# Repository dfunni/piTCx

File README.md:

# piTCx
piTCx is a Raspberry Pi based roaster control system using Artisan Roasterscope as front-end UI. A Raspberry Pi can interface with the piTCx Power HAT+ to record temperatures from up to four thermocouples as well as the temperature sensor (MCP9800) on the piTCx board. For roaster control, the Raspberry Pi can perform heater control using slow PWM (1 Hz) with the Artisan software providing PID control. Heater control requires a solid state relay connected to the OT1 jumper on the piTCx HAT+. The piTCx Power HAT+ can also power the host Raspberry Pi over GPIO through the 5V jumper connection.

# piRoast Power
The piRoast Power is a complementary board provides  5V power to supply the Raspberry Pi via the piTCx Power HAT+. Additionally, the board contains a solid state relay for heater control.

# Raspberry Pi Setup
Starting with a fresh install of the latest raspbian OS (tested with Bookworm):

1. configure the raspi with
```
sudo raspi-config
```    
In the "Advanced" menu, select expand filesystem.

In the "Interfaces" menu enable ssh, I2C, Serial Port, and Remote GPIO.

Reboot to finish the configuration.

2. Install required tools
```
sudo apt install socat
```
3. Ensure pigpiod is enabled and running
```
sudo systemctl enable pigpiod
sudo systemctl start pigpiod
```
4. Install Artisan
```
curl -L -O https://github.com/artisan-roaster-scope/artisan/releases/download/<vx.xx.x>/<artisan-linux-x.xx.x.deb>
sudo dpkg -i <artisan-linux-x.x.x.deb>
```
5. Download and setup the piTCx code
```
git clone https://github.com/dfunni/piTCx.git
cd piTCx
python -m venv env
source env/bin/activate
pip install -r requirements.txt
```
6. Create systemd service to run the piTCx command interface. First update tcxd.service line 10 to the correct login user (e.g. pi). Then:
```
sudo cp tcxd.service /etc/systemd/system/
sudo systemctl enable tcxd.service
```
From here everything is setup and ready. The next steps are to configure Artisan for communication with the TCx board.

## (Optional) Launch Artisan on boot
Copy `start_artisan.sh` to `/etc/profile.d/` with:
```
sudo cp $HOME/piTCx/start_artisan.sh /etc/profile.d/
```
# Artisan Setup
1. Go to Config > Device
    - at the top of the ET/BT tab check Control, Curves: BT, LCDs: ET and BT
    - select TC4 radio button, set ET and BT channels, set AT Channel to None, deselect PID Firmware
    - in the Extra Devices tab add the following:
        ArduinoTC4_56; Label 1: Heater; Label 2: Fan; Curve 1: enable; Curve 2: enable
        ArduinoTC4_78; Label 1: SV; Label 2: Ambient; LCD 2: enable; Curve 1: enable; Curve 2: enable

2. In Ports set Comm Port to /dev/ttyS91 with 115200-8-N-1 and change the serial Timeout to **0.4** seconds

3. Config > Sampling set to 1.0 seconds, accept the popup

4. Config > Curves select BT Projection and set to linear

5. Config > Events
     - set Event Types 2 to Heater and have that as the only event tyupe slected
     - set Default Buttons - DROP to Serial Command: OT1;0
     - under the Buttons Tab add the following
        Heater MAX; Type: Heater; Value: 100; Action: Serial Command; Documentation: OT1;{}
        Heater Off; Type: Heater; Value: 0; Action: Serial Command; Documentation: OT1;{}
        PID OFF; Type: Heater Value: 0; Action: Artisan Command; Documentation: PIDoff
    - Sliders - Event: Heater; Action: Serial Command; Command: OT1;{}

6. Config > Temperature > Celcius Mode

7. Roast > Background
    - show, BT selected
    - Load background .alog file

8. Control (Button)
    - kp: 1.30
    - ki: 0.06
    - kd: 4.50
    - Source: BT; Target - Positive: Heater; Set Value - Mode: Background; Set PID on CHARGE: enabled

# Testing piTCx on Raspberry Pi
1. Ensure Raspberry Pi setup is completed per instructions in Raspberry Pi Setup
  section. Ensure piTCx HAT+ is connected.

3. In the ~/piTCx directory run pytests with:
```
cd ~/piTCx
pytest --cov
```

3. Navigate to the ~/piTCx/tests/ directory and run:
```
cd tests/
./integration_test.sh
```
Monitor the output to ensure temperatures are read, no errors are produced.

4. Run the sample rate test to ensure 1.0 second sampling intervals are working:
```
./samprate_test.sh
```
Monitor the output to esure 10 reads are taken. Check the timestamps for 1 second accuracy. 

5. Additionally, a single Artisan command can be executed with:
```
./ArtisonCMD.sh <command> [<value>]
```
 using a command value pair from the following:
| command | value | notes |
| ------- | ----- | ----- |
| CHAN    | 1234  | Initializes the piTCx and sets order of ADC channels |
| READ    |       | No value for READ command |
| UNITS   | F/C   | Temperature units to be read |
| OT1     | 0-100 | Sets OT1 duty cycle |
| OT2     | 0-100 | Sets OT2 duty cycle |
| IO2     | 0-100 | Sets IO2 duty cycle |

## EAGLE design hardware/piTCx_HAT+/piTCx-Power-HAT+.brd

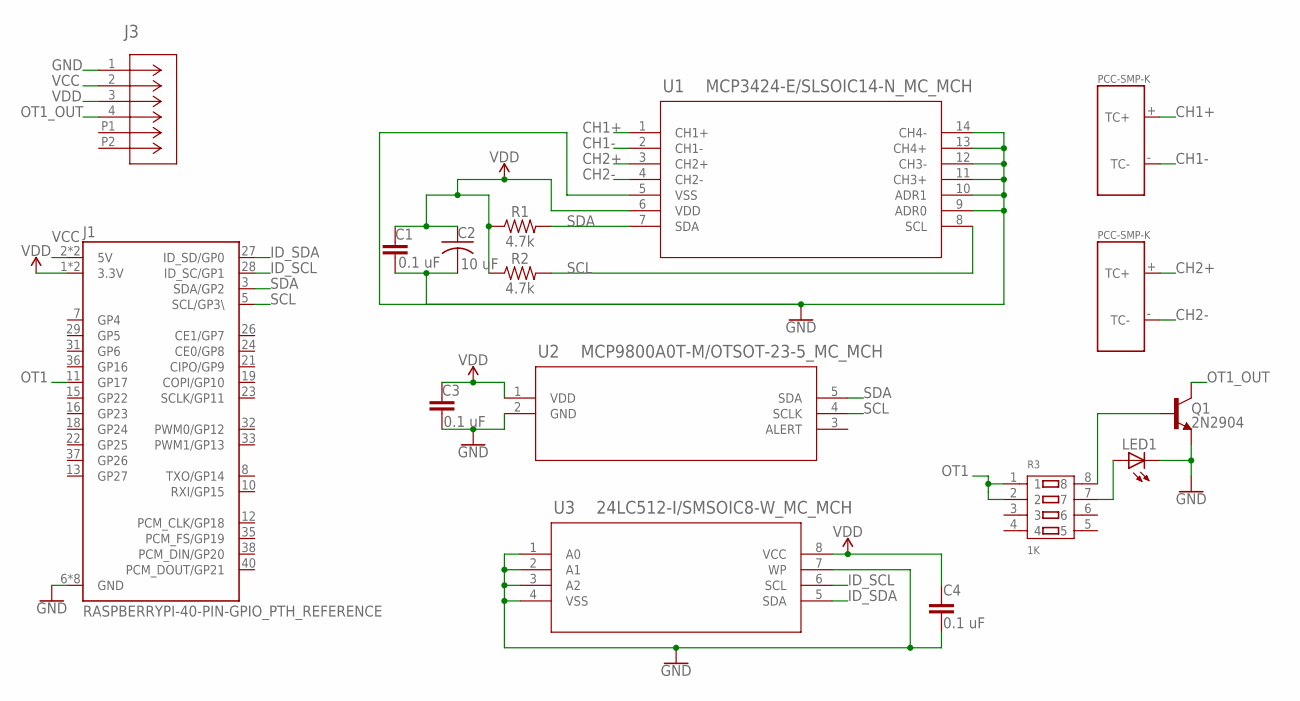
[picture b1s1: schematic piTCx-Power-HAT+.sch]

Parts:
C1, C3, C4: 0.1 uF; CAP_0805
C2: 10 uF; CAP_TANT_B; MPN T494A106M020AT
J1: RASPBERRYPI-40-PIN-GPIO_PTH_REFERENCE; RASPBERRY_PI_HAT_40_PIN_PTH_WITH_REFERNCE
J3: 436500414CON_436500414; CON_436500414
LED1: LEDCHIP-LED0805; CHIP-LED0805
Q1: 2N2904; SOT23-3
R1, R2: 4.7k; 0603
R3: 1K; RA1206-8
U1: MCP3424-E/SLSOIC14-N_MC_MCH; SOIC14-N_MC_MCH
U2: MCP9800A0T-M/OTSOT-23-5_MC_MCH; SOT-23-5_MC_MCH
U3: 24LC512-I/SMSOIC8-W_MC_MCH; SOIC8-W_MC_MCH
U$1, U$2: THERMOCOUPLECONN-PCC-SMP-K

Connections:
CH1+: U1.1 (CH1+), U$1.+ (TC+)
CH1-: U1.2 (CH1-), U$1.- (TC-)
CH2+: U1.3 (CH2+), U$2.+ (TC+)
CH2-: U1.4 (CH2-), U$2.- (TC-)
GND: C1.2, C2.2, C3.2, C4.2, J1.6 (GND), J1.9 (GND), J1.14 (GND), J1.20 (GND), J1.25 (GND), J1.30 (GND), J1.34 (GND), J1.39 (GND), J3.1, LED1.C, Q1.2 (E), U1.5 (VSS), U1.9 (ADR0), U1.10 (ADR1), U1.11 (CH3+), U1.12 (CH3-), U1.13 (CH4+), U1.14 (CH4-), U2.2 (GND), U3.1 (A0), U3.2 (A1), U3.3 (A2), U3.4 (VSS), U3.7 (WP)
ID_SCL: J1.28 (ID_SC/GP1), U3.6 (SCL)
ID_SDA: J1.27 (ID_SD/GP0), U3.5 (SDA)
unnamed: Q1.1 (B), R3.8
unnamed: LED1.A, R3.7
OT1: J1.11 (GP17), R3.1, R3.2
OT1_OUT: J3.4, Q1.3 (C)
SCL: J1.5 (SCL/GP3\), R2.2, U1.8 (SCL), U2.4 (SCLK)
SDA: J1.3 (SDA/GP2), R1.2, U1.7 (SDA), U2.5 (SDA)
VCC: J1.2 (5V), J1.4 (5V), J3.2
VDD: C1.1, C2.1, C3.1, C4.1, J1.1 (3.3V), J1.17 (3.3V), J3.3, R1.1, R2.1, U1.6 (VDD), U2.1 (VDD), U3.8 (VCC)

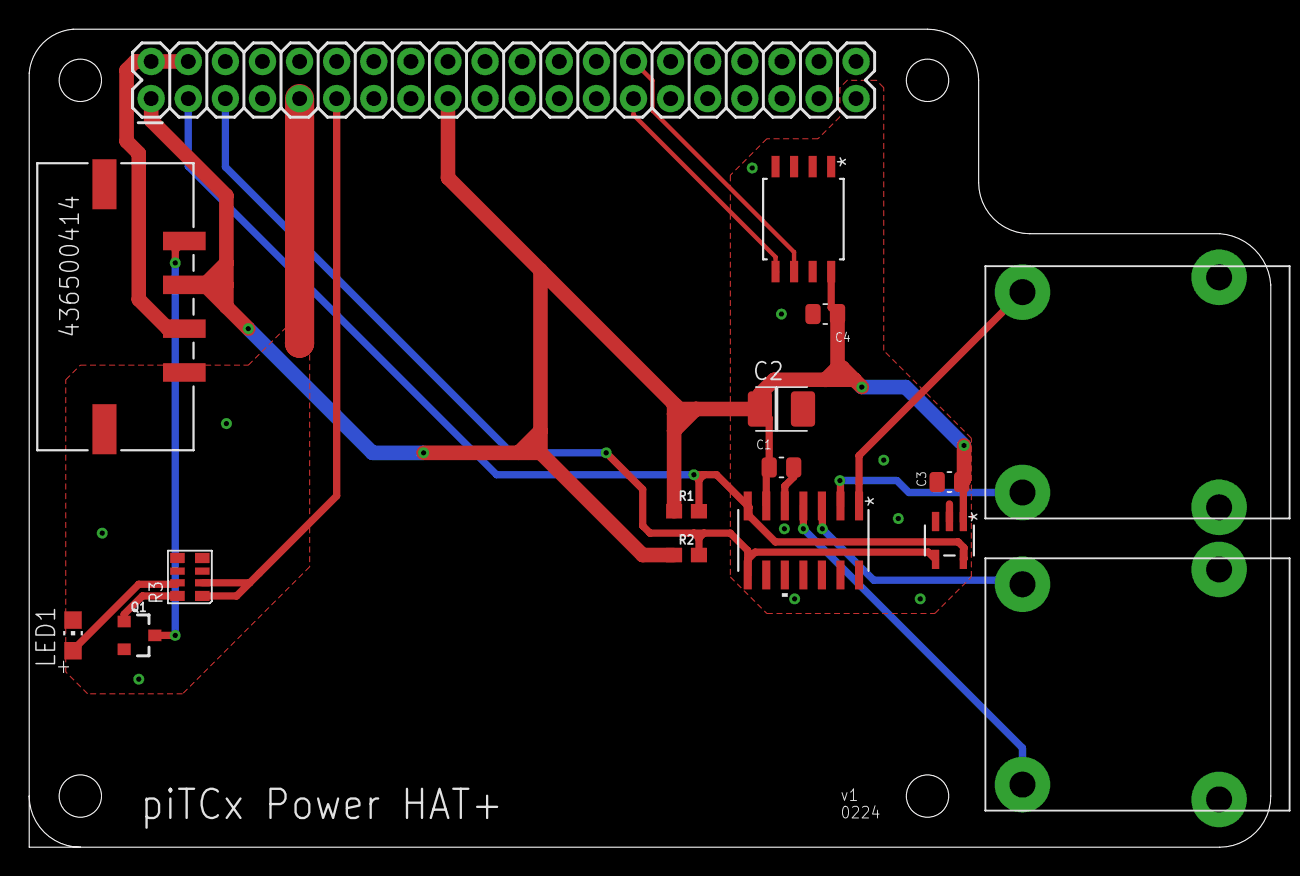
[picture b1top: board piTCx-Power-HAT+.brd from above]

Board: 2 copper layers, 85.0 x 56.0 mm, 16 parts (0 on the bottom side), 15 nets.

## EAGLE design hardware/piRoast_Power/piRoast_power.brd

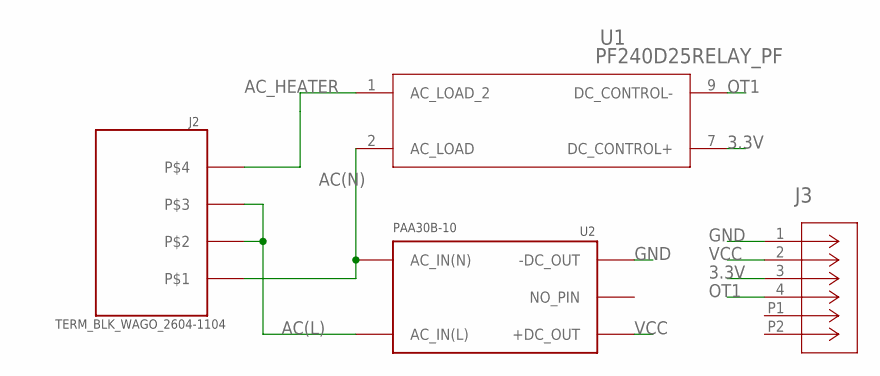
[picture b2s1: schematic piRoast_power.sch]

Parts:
J2: TERM_BLK_WAGO_2604-1104
J3: 436500414CON_436500414; CON_436500414
U1: PF240D25RELAY_PF; RELAY_PF
U2: PAA30B-10

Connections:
3.3V: J3.3, U1.7 (DC_CONTROL+)
AC(L): J2.P1, J2.P2, J2.P5, J2.P6, U2.AC_IN(L)
AC(N): J2.P3, J2.P4, U1.2 (AC_LOAD), U2.AC_IN(N)
AC_HEATER: J2.P0, J2.P7, U1.1 (AC_LOAD_2)
GND: J3.1, U2.-DC_OUT
OT1: J3.4, U1.9 (DC_CONTROL-)
VCC: J3.2, U2.+DC_OUT

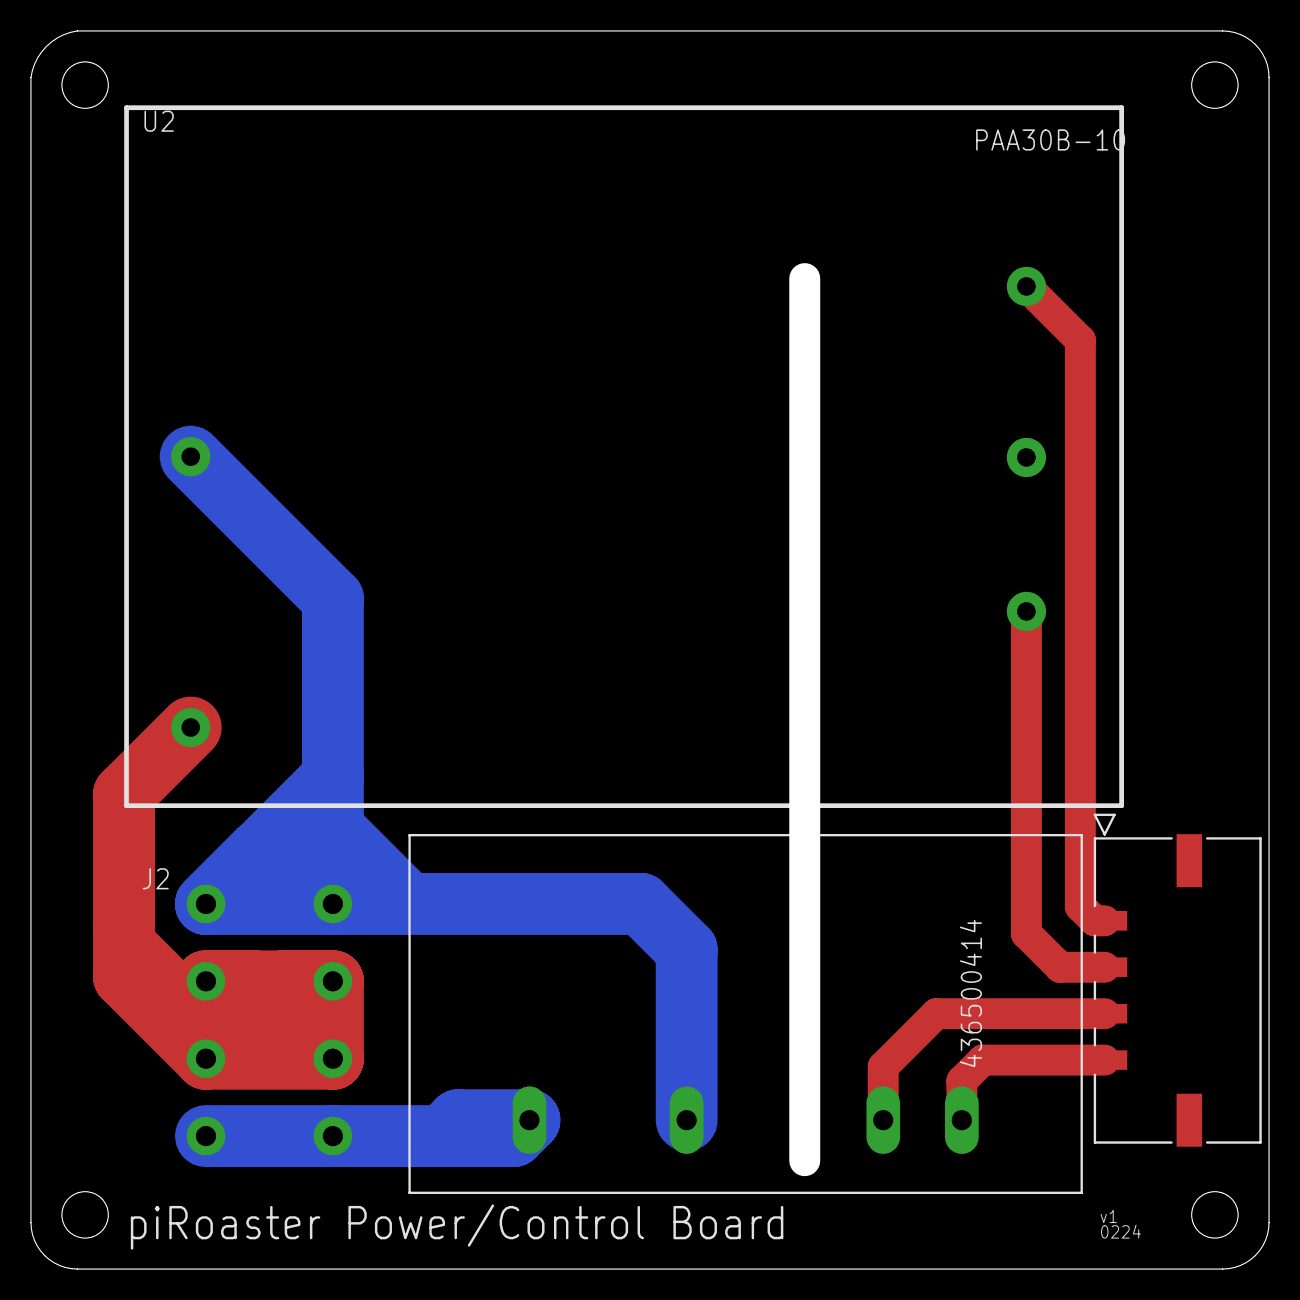
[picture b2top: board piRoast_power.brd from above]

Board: 2 copper layers, 80.0 x 80.0 mm, 4 parts (0 on the bottom side), 7 nets.

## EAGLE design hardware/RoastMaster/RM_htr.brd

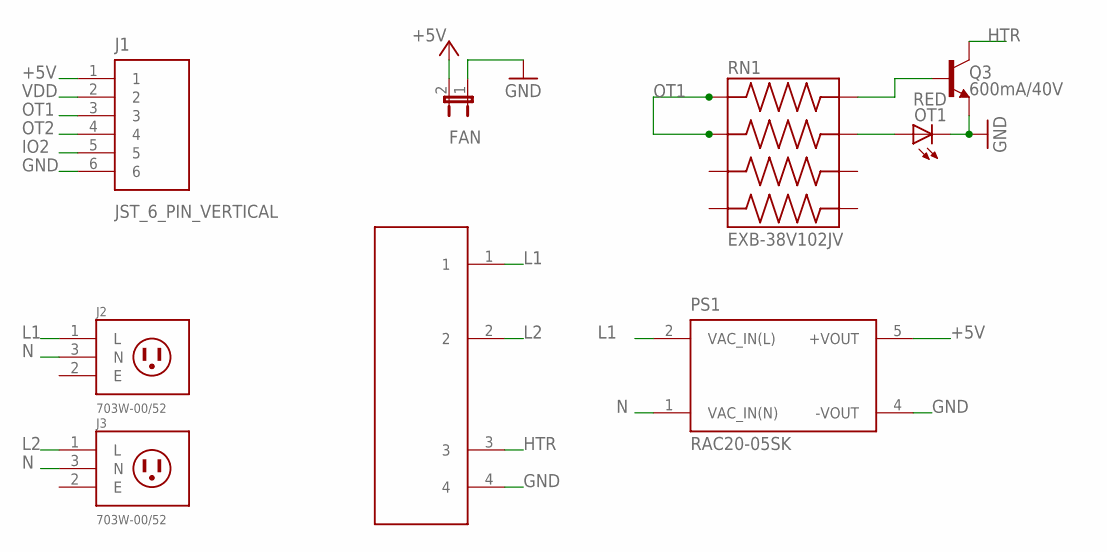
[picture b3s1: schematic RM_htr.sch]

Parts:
FAN: JP1E; JP1
J1: JST_6_PIN_VERTICAL; JST-6-SMD-VERT-1.0MM
J2, J3: 703W-00/52; QUALTEK_703W-00/52
OT1: RED; CHIPLED_0805
PS1: RAC20-05SK; CONV_RAC20-05SK
Q3: 600mA/40V; SOT23-3
RN1: EXB-38V102JV; RESCAXS80P320X160X60-8N
U$1: PF240D25X

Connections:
+5V: FAN.2, J1.1, PS1.5 (+VOUT)
E: J2.2 (E), J3.2 (E)
GND: FAN.1, J1.6, OT1.C, PS1.4 (-VOUT), Q3.2 (E), U$1.4
HTR: Q3.3 (C), U$1.3
IO2: J1.5
L1: J2.1 (L), PS1.2 (VAC_IN(L)), U$1.1
L2: J3.1 (L), U$1.2
N: J2.3 (N), J3.3 (N), PS1.1 (VAC_IN(N))
unnamed: Q3.1 (B), RN1.8
unnamed: OT1.A, RN1.7
OT1: J1.3, RN1.1, RN1.2
OT2: J1.4
VDD: J1.2

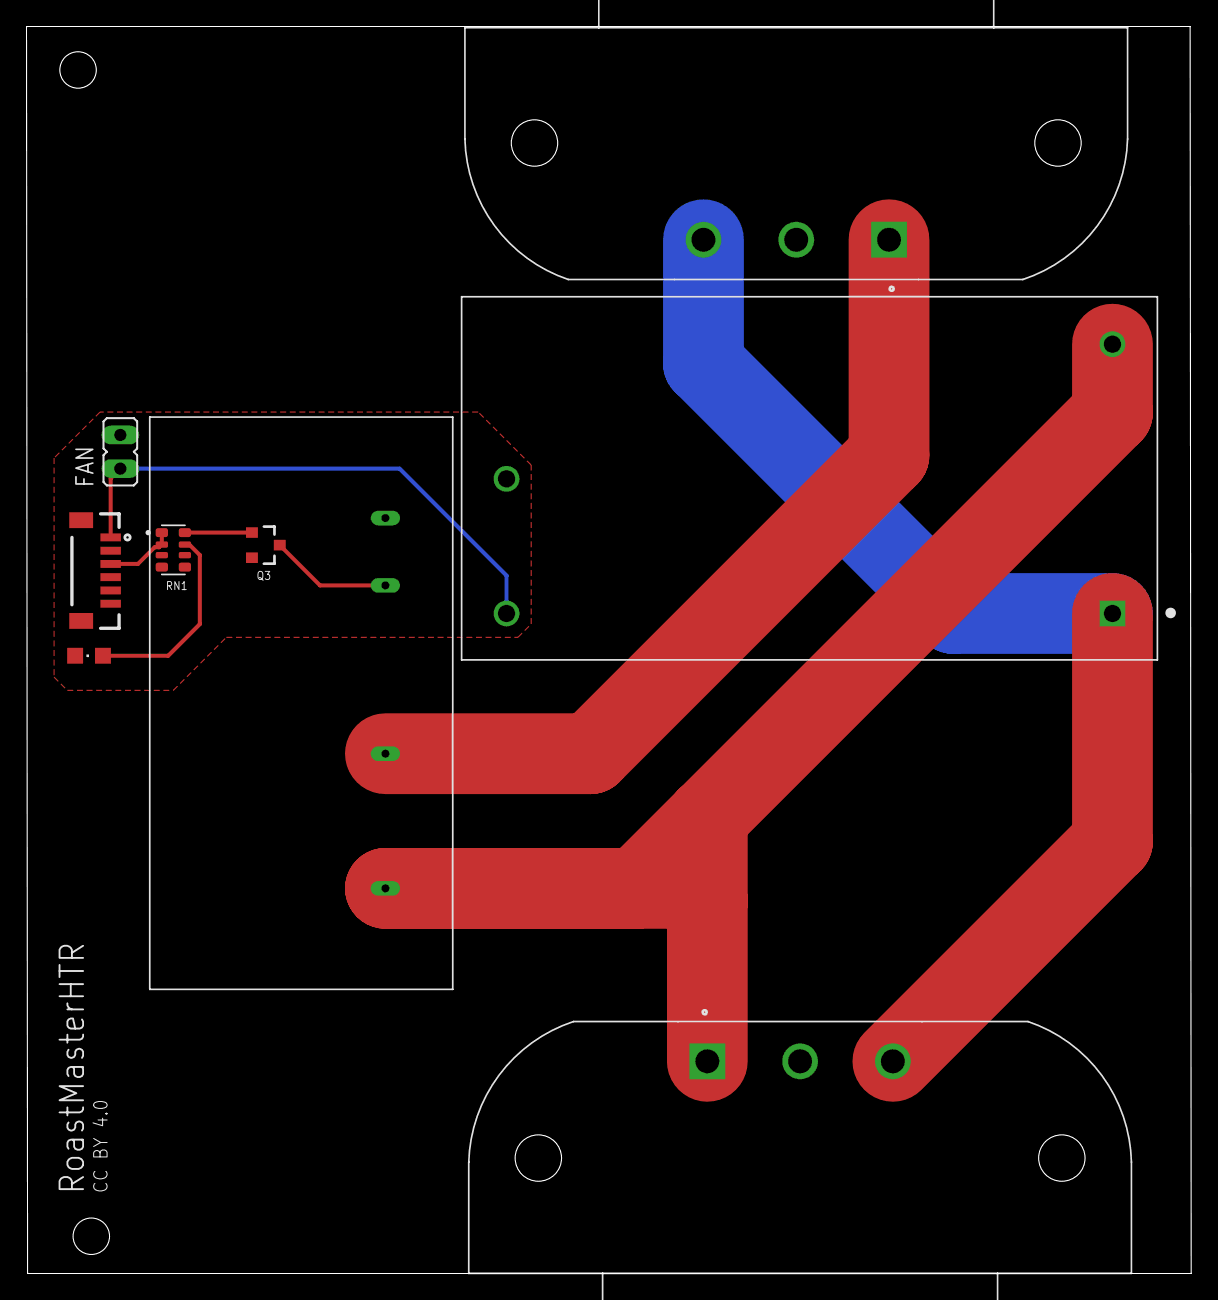
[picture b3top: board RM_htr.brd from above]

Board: 2 copper layers, 87.9 x 94.1 mm, 9 parts (0 on the bottom side), 10 nets.

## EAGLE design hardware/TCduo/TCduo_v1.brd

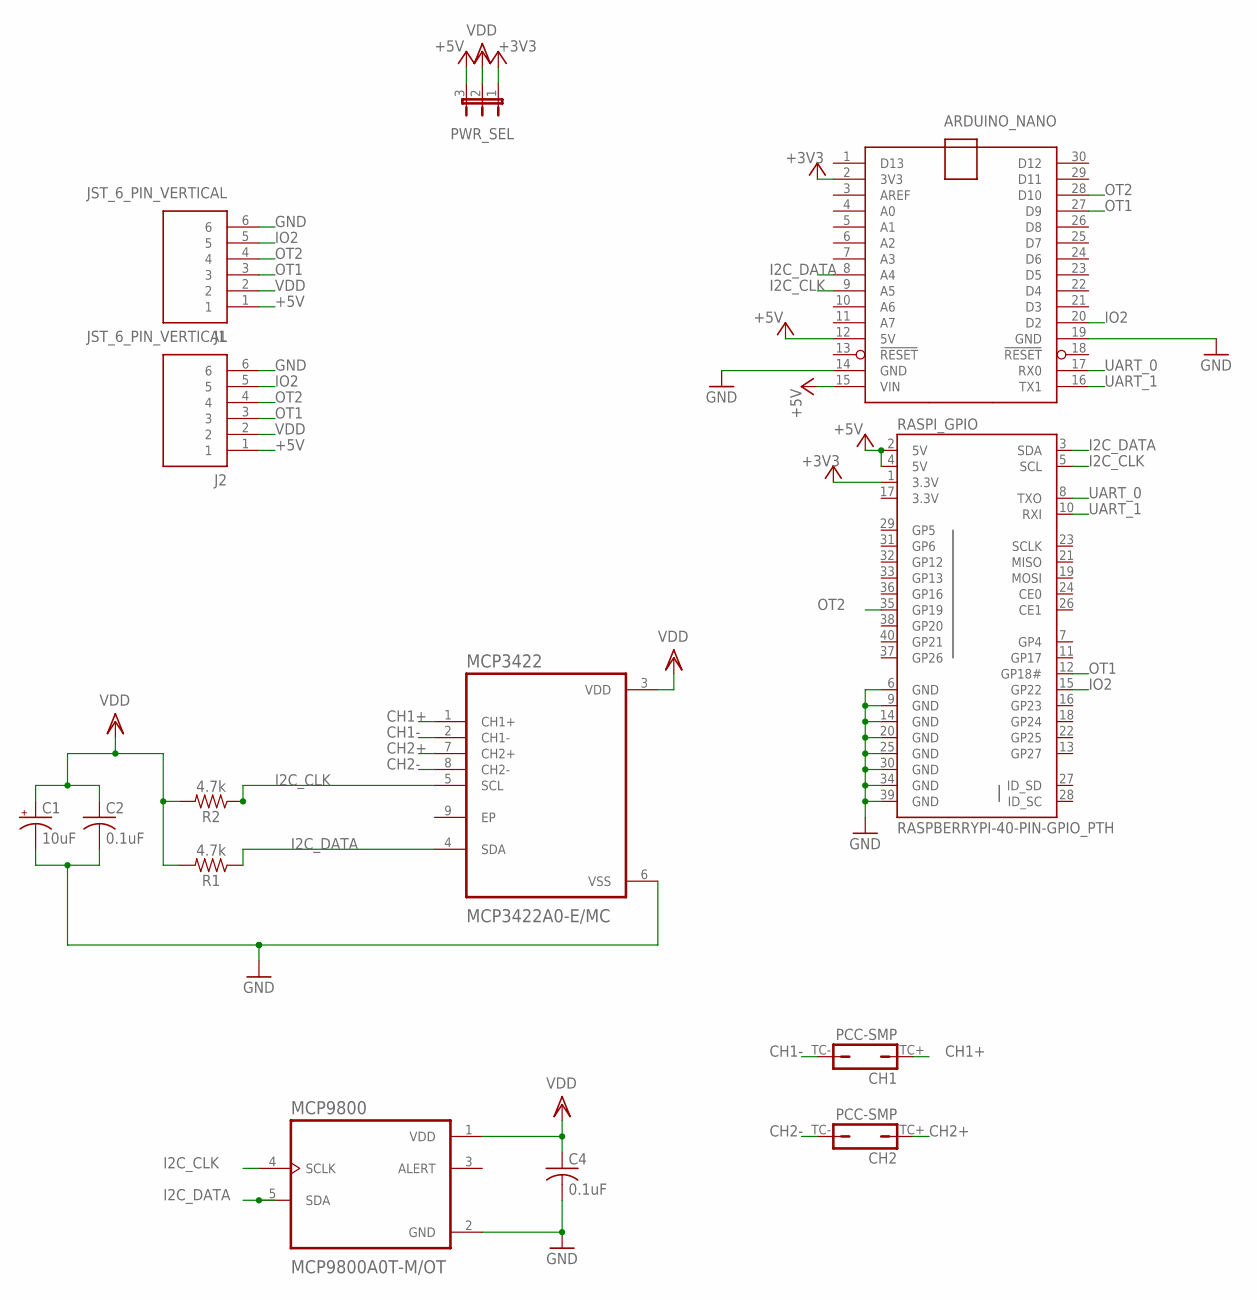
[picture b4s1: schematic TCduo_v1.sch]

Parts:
ARDUINO_NANO: ARDUINO_NANO
C1: 10uF; EIA3216
C2, C4: 0.1uF; C0805
CH1, CH2: PCC-SMP
J1, J2: JST_6_PIN_VERTICAL; JST-6-SMD-VERT-1.0MM
MCP3422: MCP3422A0-E/MC; SON50P200X300X100-9N
MCP9800: MCP9800A0T-M/OT; SOT95P270X145-5N
PWR_SEL: JP2E; JP2
R1, R2: 4.7k; 0603
RASPI_GPIO: RASPBERRYPI-40-PIN-GPIO_PTH; 2X20_SHROUDED

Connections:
3.3V: RASPI_GPIO.17 (3.3V)
+3V3: ARDUINO_NANO.2 (3V3), PWR_SEL.1, RASPI_GPIO.1 (3.3V)
+5V: ARDUINO_NANO.12 (5V), ARDUINO_NANO.15 (VIN), J1.1, J2.1, PWR_SEL.3, RASPI_GPIO.2 (5V), RASPI_GPIO.4 (5V)
CH1+: CH1.TC+ (1), MCP3422.1 (CH1+)
CH1-: CH1.TC- (2), MCP3422.2 (CH1-)
CH2+: CH2.TC+ (1), MCP3422.7 (CH2+)
CH2-: CH2.TC- (2), MCP3422.8 (CH2-)
GND: ARDUINO_NANO.14 (GND), ARDUINO_NANO.19 (GND), C1.-, C2.2, C4.2, J1.6, J2.6, MCP3422.6 (VSS), MCP9800.2 (GND), RASPI_GPIO.6 (GND), RASPI_GPIO.9 (GND), RASPI_GPIO.14 (GND), RASPI_GPIO.20 (GND), RASPI_GPIO.25 (GND), RASPI_GPIO.30 (GND), RASPI_GPIO.34 (GND), RASPI_GPIO.39 (GND)
I2C_CLK: ARDUINO_NANO.9 (A5), MCP3422.5 (SCL), MCP9800.4 (SCLK), R2.1, RASPI_GPIO.5 (SCL)
I2C_DATA: ARDUINO_NANO.8 (A4), MCP3422.4 (SDA), MCP9800.5 (SDA), R1.1, RASPI_GPIO.3 (SDA)
IO2: ARDUINO_NANO.20 (D2), J1.5, J2.5, RASPI_GPIO.15 (GP22)
OT1: ARDUINO_NANO.27 (D9), J1.3, J2.3, RASPI_GPIO.12 (GP18#)
OT2: ARDUINO_NANO.28 (D10), J1.4, J2.4, RASPI_GPIO.35 (GP19)
UART_0: ARDUINO_NANO.17 (RX0), RASPI_GPIO.8 (TXO)
UART_1: ARDUINO_NANO.16 (TX1), RASPI_GPIO.10 (RXI)
VDD: C1.+, C2.1, C4.1, J1.2, J2.2, MCP3422.3 (VDD), MCP9800.1 (VDD), PWR_SEL.2, R1.2, R2.2

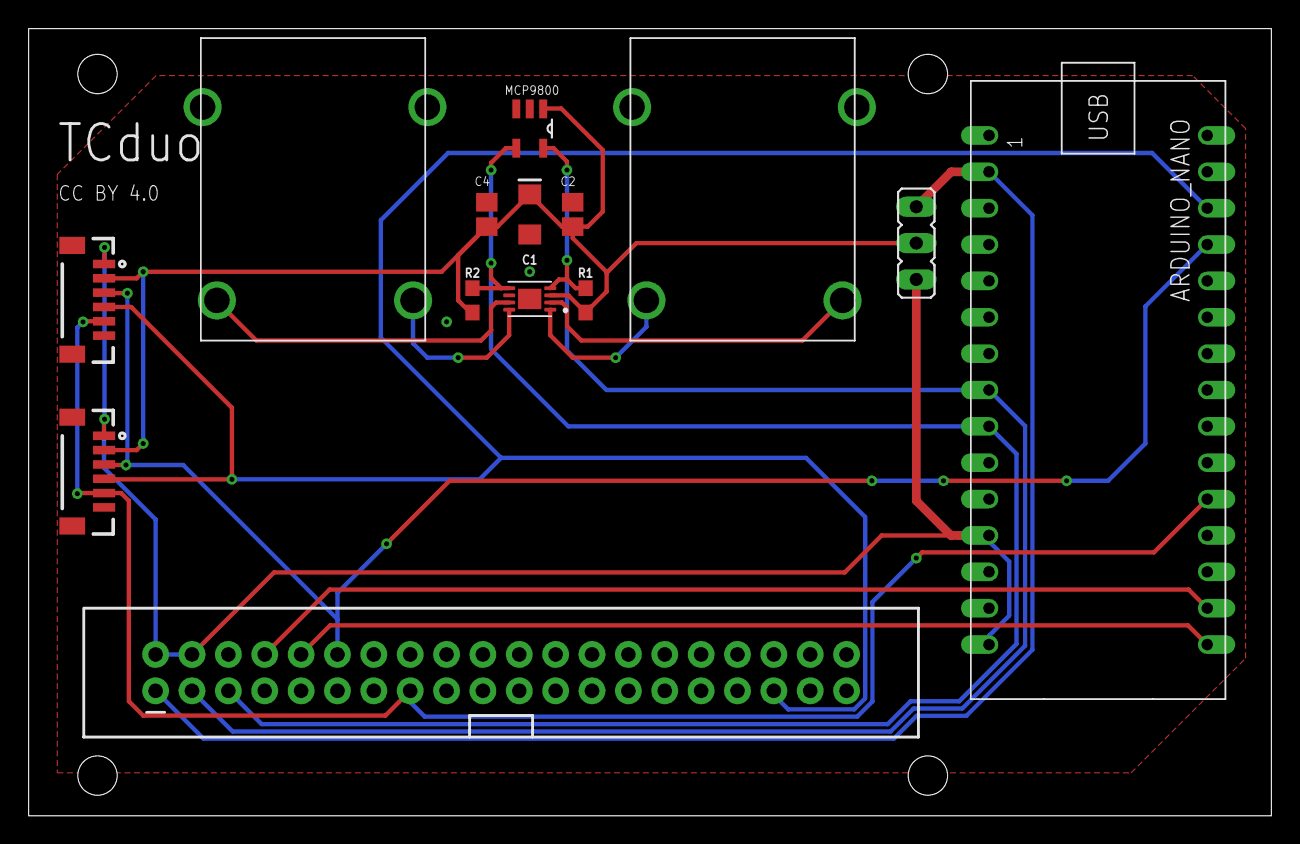
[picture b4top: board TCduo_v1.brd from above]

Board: 2 copper layers, 86.8 x 55.0 mm, 14 parts (0 on the bottom side), 15 nets.

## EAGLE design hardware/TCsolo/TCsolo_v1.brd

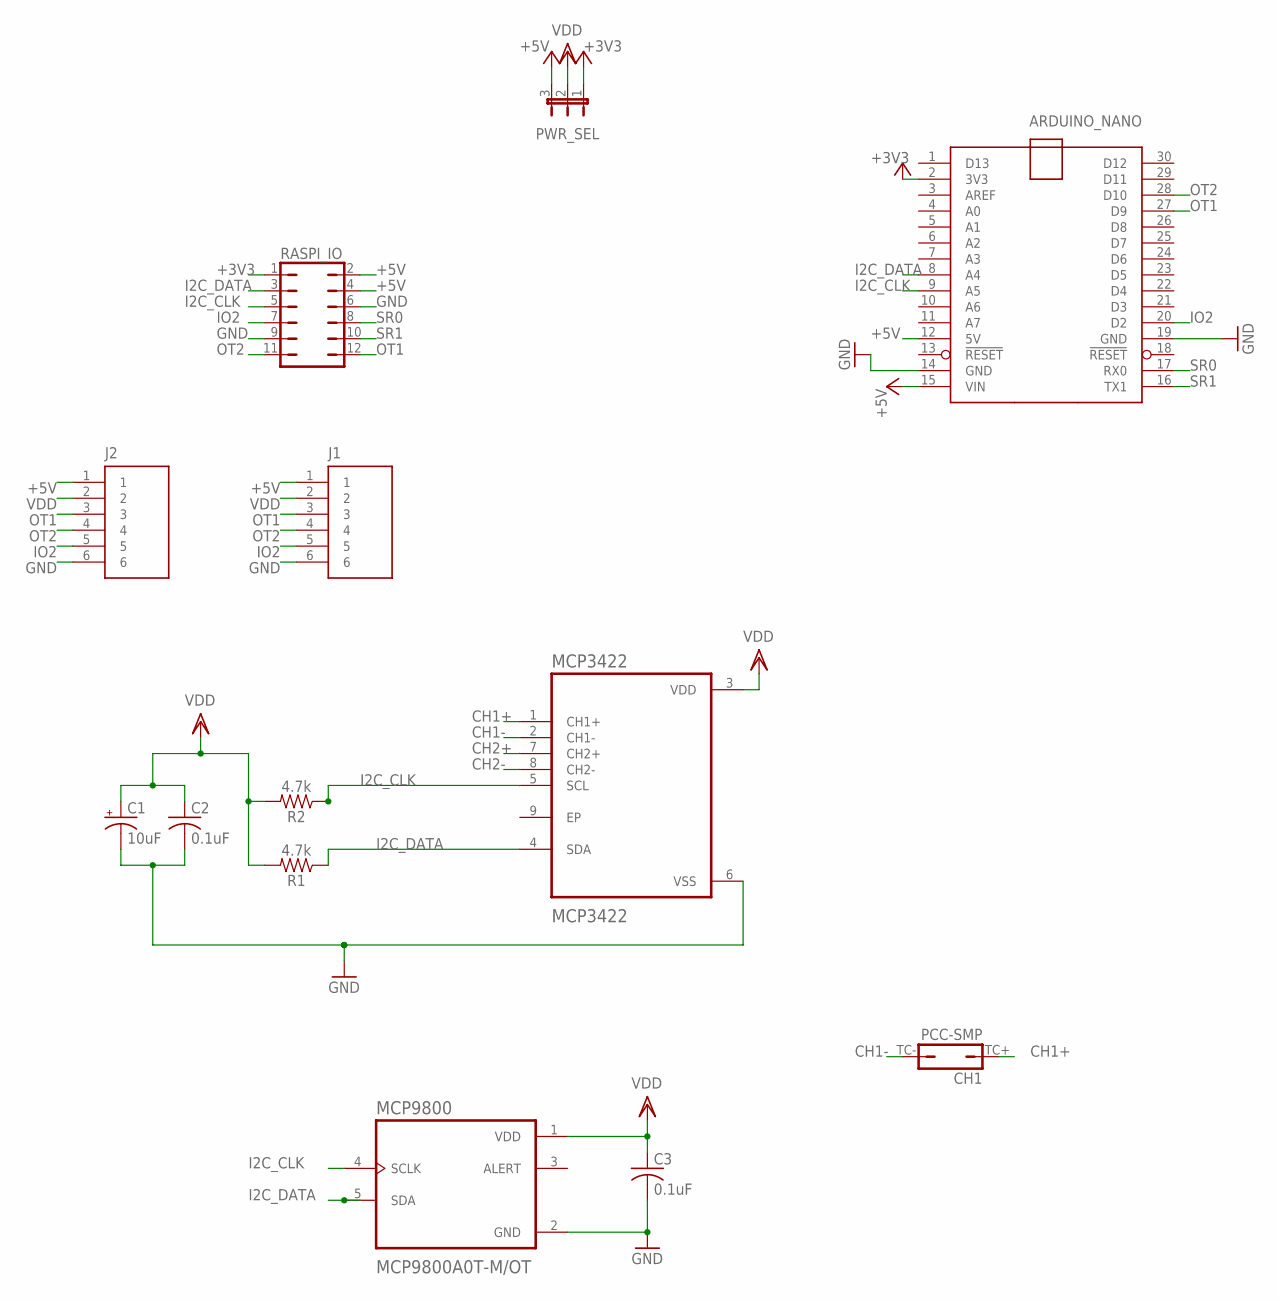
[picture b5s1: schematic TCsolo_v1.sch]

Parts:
ARDUINO_NANO: ARDUINO_NANO
C1: 10uF; EIA3216
C2, C3: 0.1uF; C0805
CH1: PCC-SMP
J1, J2: JST_6_PIN_VERTICAL; JST-6-SMD-VERT-1.0MM
MCP3422: MCP3422; SON50P200X300X100-9N
MCP9800: MCP9800A0T-M/OT; SOT95P270X145-5N
PWR_SEL: JP2E; JP2
R1, R2: 4.7k; 0603
RASPI_IO: JP6Q

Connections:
+3V3: ARDUINO_NANO.2 (3V3), PWR_SEL.1, RASPI_IO.1
+5V: ARDUINO_NANO.12 (5V), ARDUINO_NANO.15 (VIN), J1.1, J2.1, PWR_SEL.3, RASPI_IO.2, RASPI_IO.4
CH1+: CH1.TC+ (1), MCP3422.1 (CH1+)
CH1-: CH1.TC- (2), MCP3422.2 (CH1-)
CH2+: MCP3422.7 (CH2+)
CH2-: MCP3422.8 (CH2-)
GND: ARDUINO_NANO.14 (GND), ARDUINO_NANO.19 (GND), C1.-, C2.2, C3.2, J1.6, J2.6, MCP3422.6 (VSS), MCP9800.2 (GND), RASPI_IO.6, RASPI_IO.9
I2C_CLK: ARDUINO_NANO.9 (A5), MCP3422.5 (SCL), MCP9800.4 (SCLK), R2.1, RASPI_IO.5
I2C_DATA: ARDUINO_NANO.8 (A4), MCP3422.4 (SDA), MCP9800.5 (SDA), R1.1, RASPI_IO.3
IO2: ARDUINO_NANO.20 (D2), J1.5, J2.5, RASPI_IO.7
OT1: ARDUINO_NANO.27 (D9), J1.3, J2.3, RASPI_IO.12
OT2: ARDUINO_NANO.28 (D10), J1.4, J2.4, RASPI_IO.11
SR0: ARDUINO_NANO.17 (RX0), RASPI_IO.8
SR1: ARDUINO_NANO.16 (TX1), RASPI_IO.10
VDD: C1.+, C2.1, C3.1, J1.2, J2.2, MCP3422.3 (VDD), MCP9800.1 (VDD), PWR_SEL.2, R1.2, R2.2

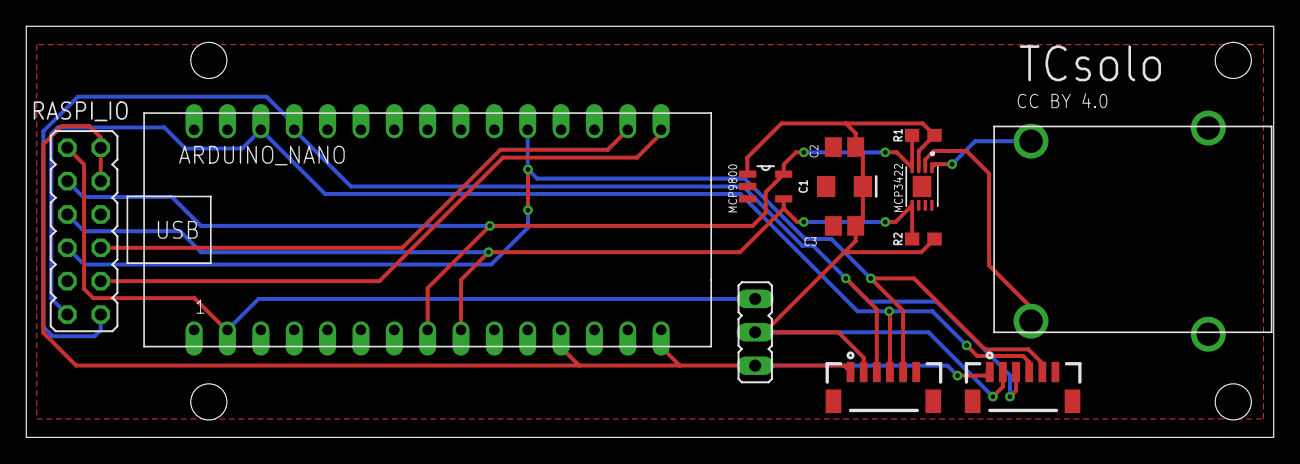
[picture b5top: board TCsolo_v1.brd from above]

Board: 2 copper layers, 95.0 x 31.3 mm, 13 parts (0 on the bottom side), 13 nets.

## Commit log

2020-12-30 added gitignore
2021-01-02 code to read thermocouple and ambient temperature over I2C
2021-01-03 cleaned up device drivers
2021-01-03 updated test script for new drivers
2021-01-04 moved temperature conversion utils to thermocouple.py
2021-01-06 modified device drivers, added artisan communication code
2021-01-11 added 1Hz pwm control of OT1
2021-01-11 minor changes
2021-01-11 corrected pins
2021-01-18 initial commit of hardware and updated docs
2021-01-18 renamed hardware files
2021-01-19 added pi setup to readme
2021-01-21 renamed files
2021-01-21 updated imports
2021-01-21 updated hardware
2021-01-29 updated hardware configs
2021-01-30 removed ymltst.py
2021-01-30 updated test scripts
2021-02-07 resolution bug fix
2021-02-07 converted to absolute references
2021-02-07 added arduino pinout
2021-02-07 updated .gitignore
2021-02-10 added filter handling
2021-02-10 changed to start scipts from /home/pi
2021-02-10 added instructions for running at boot
2021-03-07 modified boot procedures and scripts
2021-03-07 added Artisan Button handeling
2021-03-09 standardized logging
2021-03-28 handle no io
2021-03-28 added handling of charge button
2023-09-19 security updates
2023-12-15 updates to readability and code standardization
2023-12-15 minor readability updates
2023-12-15 added requirements
2023-12-16 Updated README for Raspbian Bookworm setup
2023-12-17 docs cleanup
2023-12-17 converted to run as daemon with systemd
2023-12-17 reorganized file tree
2023-12-18 added Artisan setup information
2023-12-19 sample interval bug fix
2023-12-20 updated serial timeout configuration
2023-12-20 changed ADC resolution to 16 bit
2024-02-23 HAT+ hardware v1 updates
2024-02-23 updates for repo name change
2024-02-23 updated install steps
2024-02-23 upated logging
2024-02-23 Update README.md with pictures
2024-02-24 added pytest for MCP9800
2024-02-24 pytest complete for MCP342x
2024-02-24 updated samprate_test
2024-02-24 removed unused imports
2024-02-24 updated test procedures
2024-02-25 added tests and refactored thermocouple
2024-02-26 added ID eeprom configuration
2024-03-04 corrected spelling error
2024-03-09 added default profile
2024-03-09 added artisan theme
2024-03-09 added artisan settings and config
2024-03-14 corrected PID settings in artisan
2024-03-16 updated settings and profile to fix control bug where target defaults to ET

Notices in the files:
hardware/RoastMaster/RM_htr.brd:
CC BY 4.0
parts and their libraries:
SparkFun-DiscreteSemi: Licensing: Creative Commons ShareAlike 4.0 International - https://creativecommons.org/licenses/by-sa/4.0
COPYRIGHT: Copyright (C) 2023 Ultra Librarian. All rights reserved.
COPYRIGHT: Copyright (C) 2024 Ultra Librarian. All rights reserved.
